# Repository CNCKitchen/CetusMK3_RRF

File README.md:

# CetusMK3_RRF
Cetus MK3 conversion to a RepRapFirmware mainboard.
# Introduction
This repository contains all the files and resources I used to convert my CETUS MK3 to a RepRapFirmware mainboard, more precisely the Mellow FLY RRF E3.
# Contents
## Adapter Board
Contains the KiCAD and GERBER files to manufacture your own board.
## Holder
Contains different holders to mount the adapter board and the new mainboard. Available versions:
- Mellow Fly RRF E3 (and E3 Pro)
## PrusaSlicer Profile
Contains the PS profile with wich I did most of my prints. Created with PS2.4 Beta but should also be back-compatible.
## RRF Configuration
Contains the configuration files for Reprap Firmware.
- Created for RepRap Firmware 3.4
- Created for Mellow Fly RRF E3
- Thermistor of the hotend was swapped to a standard E3D cartrige style thermistor

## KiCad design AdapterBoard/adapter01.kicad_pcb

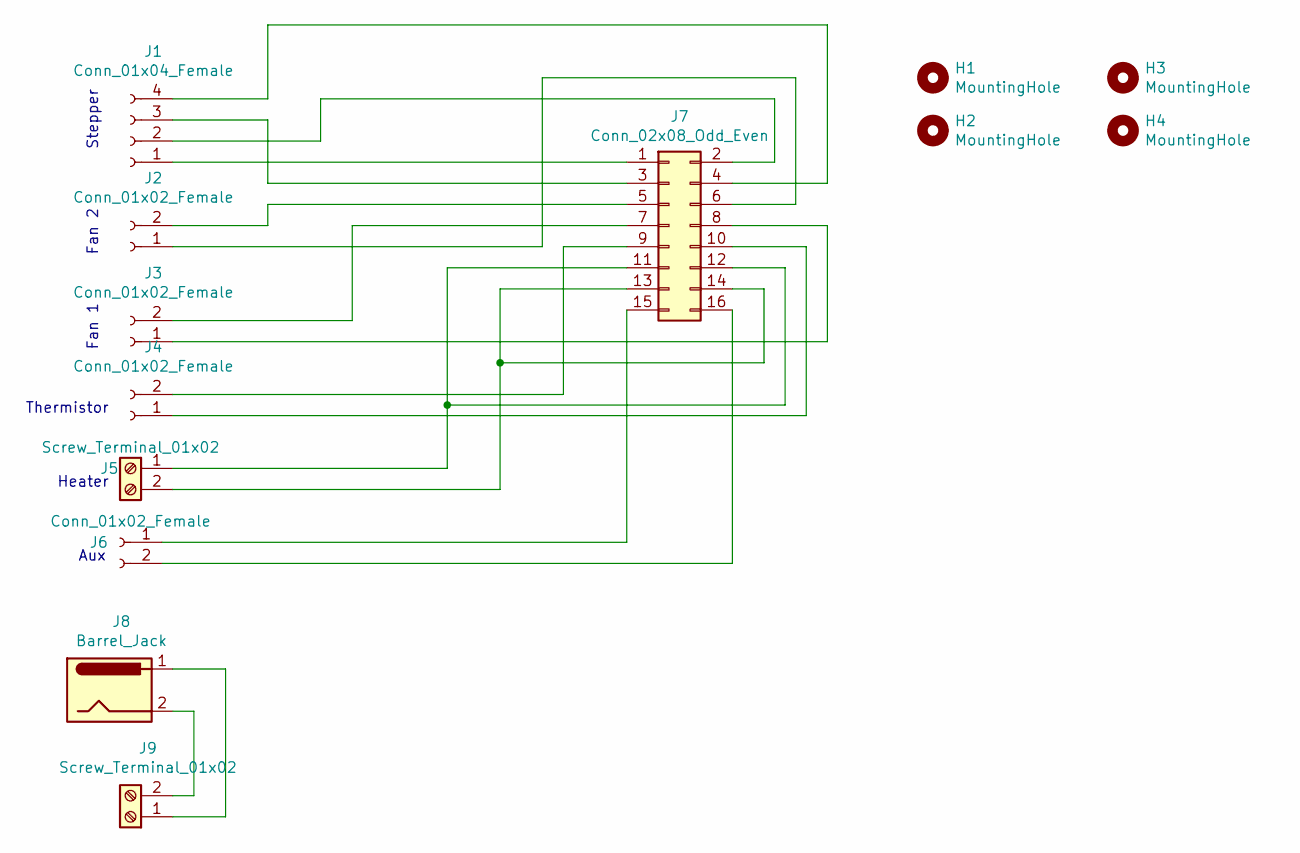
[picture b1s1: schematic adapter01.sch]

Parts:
H1, H2, H3, H4: MountingHole; MountingHole_3.5mm
J1: Conn_01x04_Female; JST_XH_B4B-XH-A_1x04_P2.50mm_Vertical
J2, J3, J4, J6: Conn_01x02_Female; JST_XH_B2B-XH-A_1x02_P2.50mm_Vertical
J5, J9: Screw_Terminal_01x02; TerminalBlock_Phoenix_MKDS-1,5-2-5.08_1x02_P5.08mm_Horizont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
J7: Conn_02x08_Odd_Even; IDC-Header_2x08_P2.54mm_Vertical
J8: Barrel_Jack; BarrelJack_Horizontal

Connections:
unnamed: J1.1, J7.1
unnamed: J1.2, J7.2
unnamed: J1.3, J7.3
unnamed: J1.4, J7.4
unnamed: J2.1, J7.6
unnamed: J2.2, J7.5
unnamed: J3.1, J7.8
unnamed: J3.2, J7.7
unnamed: J4.1, J7.10
unnamed: J4.2, J7.9
unnamed: J5.1, J7.11, J7.12
unnamed: J5.2, J7.13, J7.14
unnamed: J6.1, J7.15
unnamed: J6.2, J7.16
unnamed: J8.1, J9.1
unnamed: J8.2, J9.2

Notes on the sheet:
Stepper
Fan 2
Fan 1
Thermistor
Heater
Aux

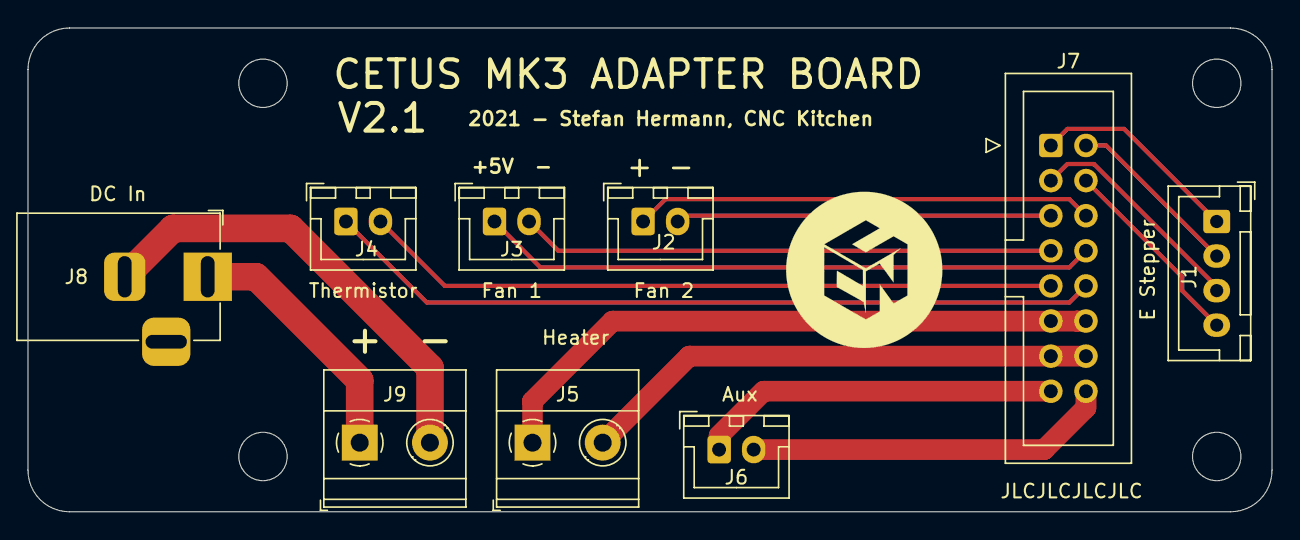
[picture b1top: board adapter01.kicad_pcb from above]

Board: 2 copper layers, 90.0 x 35.0 mm, 13 parts (0 on the bottom side), 16 nets.

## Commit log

2021-12-11 added PrusaSlicer profile 0.2mm
2021-12-11 Added CAD models
